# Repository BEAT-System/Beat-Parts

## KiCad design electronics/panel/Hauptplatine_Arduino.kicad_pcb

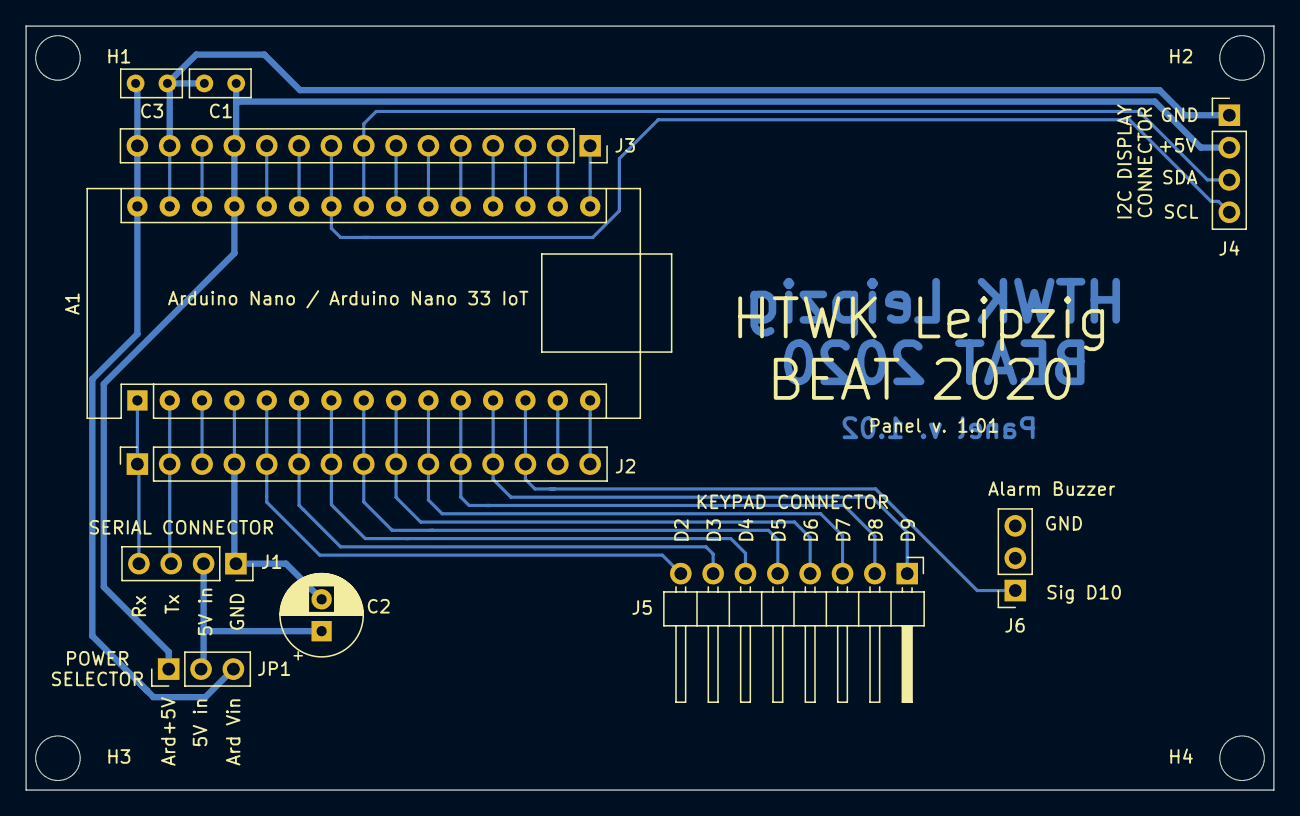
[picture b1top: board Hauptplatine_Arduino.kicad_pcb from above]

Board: 2 copper layers, 98.0 x 60.0 mm, 15 parts (0 on the bottom side), 30 nets.

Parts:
A1: Arduino_Nano_v3.x; Arduino_Nano
C1, C3: 100n; C_Rect_L4.6mm_W2.0mm_P2.50mm_MKS02_FKP02
C2: 100µ; CP_Radial_D6.3mm_P2.50mm
H1, H2, H3, H4: MountingHole; MountingHole_3.5mm
J1: Conn_01x04_Female; PinSocket_1x04_P2.54mm_Vertical
J2: Arduino Connector 1; PinSocket_1x15_P2.54mm_Vertical
J3: Arduino Connector 2; PinSocket_1x15_P2.54mm_Vertical
J4: I2C-1-5V; PinHeader_1x04_P2.54mm_Vertical
J5: Conn_01x08_Female; PinHeader_1x08_P2.54mm_Horizontal
J6: Conn_01x03_Female; PinSocket_1x03_P2.54mm_Vertical
JP1: Jumper_NC_Dual; PinHeader_1x03_P2.54mm_Vertical

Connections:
+3V3: A1.17, J3.2
+5V: C2.1, J1.2, JP1.2
A0: A1.19, J3.4
A1: A1.20, J3.5
A2: A1.21, J3.6
A3: A1.22, J3.7
A4: A1.23, J3.8, J4.3
A5: A1.24, J3.9, J4.4
A6: A1.25, J3.10
A7: A1.26, J3.11
AREF: A1.18, J3.3
Ard_+5V: A1.27, C1.2, J3.12, J4.2, JP1.1
D0: A1.2, J1.3, J2.2
D1: A1.1, J1.4, J2.1
D2: A1.5, J2.5, J5.8
D3: A1.6, J2.6, J5.7
D4: A1.7, J2.7, J5.6
D5: A1.8, J2.8, J5.5
D6: A1.9, J2.9, J5.4
D7: A1.10, J2.10, J5.3
D8: A1.11, J2.11, J5.2
D9: A1.12, J2.12, J5.1
D10: A1.13, J2.13, J6.1
D11: A1.14, J2.14
D12: A1.15, J2.15
D13: A1.16, J3.1
GND: A1.4, A1.29, C1.1, C2.2, C3.2, J1.1, J2.4, J3.14, J4.1, J6.3
RESET3: A1.3, J2.3
RESET28: A1.28, J3.13
VIN: A1.30, C3.1, J3.15, JP1.3
